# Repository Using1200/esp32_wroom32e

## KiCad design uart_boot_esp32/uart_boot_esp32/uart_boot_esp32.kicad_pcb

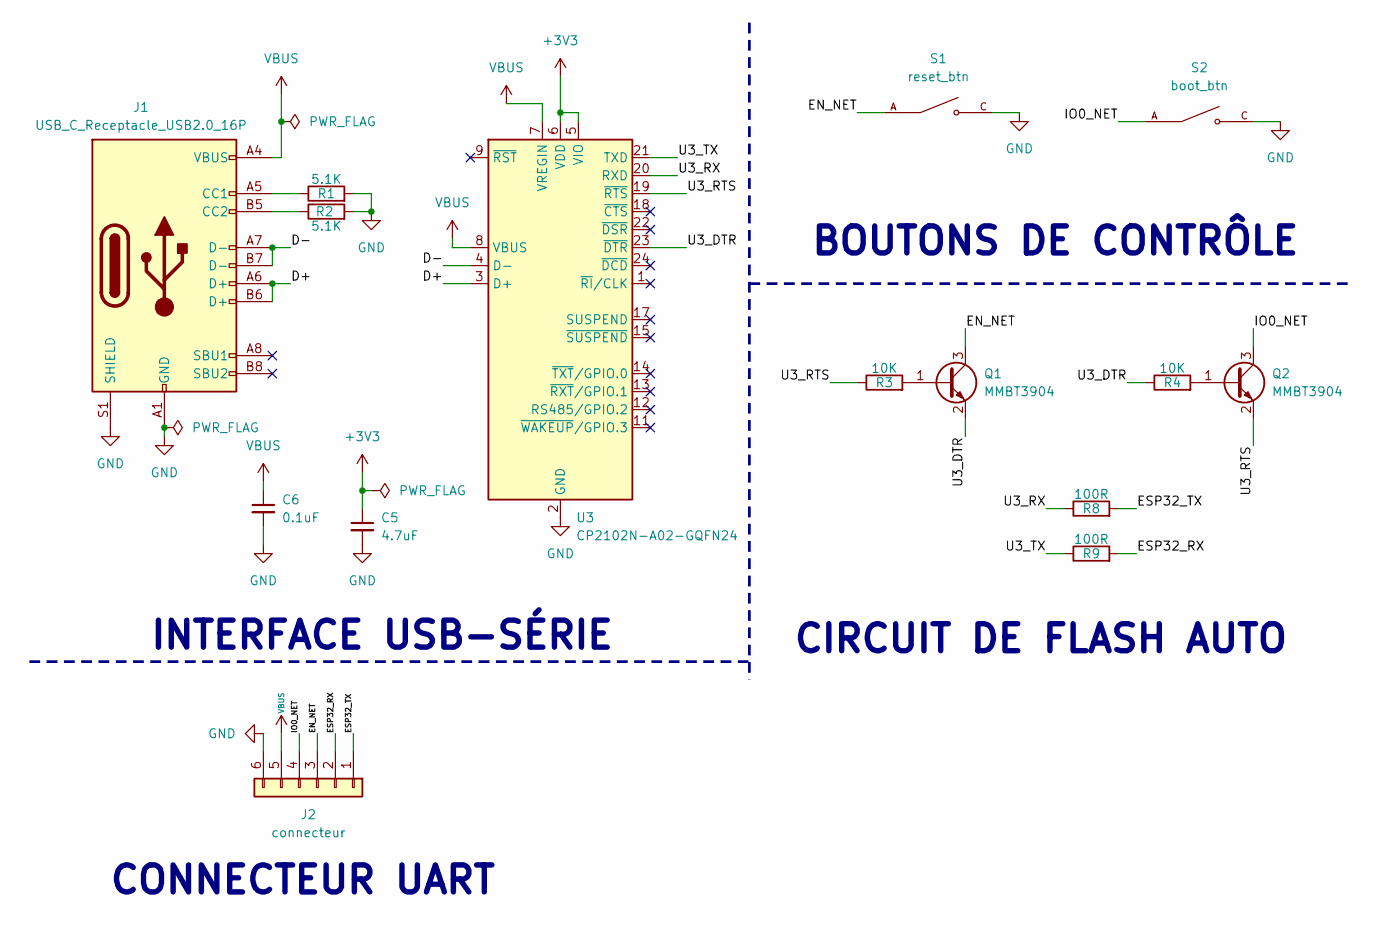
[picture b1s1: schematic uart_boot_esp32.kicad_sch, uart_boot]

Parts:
C5: 4.7uF; C_0603_1608Metric; LCSC C8032
C6: 0.1uF; C_0603_1608Metric; LCSC C14663
J1: USB_C_Receptacle_USB2.0_16P; USB_C_Receptacle_GCT_USB4105-xx-A_16P_TopMnt_Horizontal; LCSC C393939
J2: connecteur; Hirose_FH12-6S-0.5SH_1x06-1MP_P0.50mm_Horizontal
Q1, Q2: MMBT3904; SOT-23; LCSC C20526
R1, R2: 5.1K; R_0603_1608Metric; LCSC C23186
R3, R4: 10K; R_0603_1608Metric; LCSC C25804
R8, R9: 100R; R_0603_1608Metric; LCSC C22775
S1: reset_btn; SW_TS-1187A-B-A-B; PARTREV A0; LCSC C318884
S2: boot_btn; SW_TS-1187A-B-A-B; PARTREV A0; LCSC C318884
U3: CP2102N-A02-GQFN24; QFN-24-1EP_4x4mm_P0.5mm_EP2.6x2.6mm; LCSC C969151

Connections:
+3V3: C5.1, U3.5 (VIO), U3.6 (VDD)
/D+: J1.A6 (D+), J1.B6 (D+), U3.3 (D+)
/D-: J1.A7 (D-), J1.B7 (D-), U3.4 (D-)
/EN_NET: J2.3, Q1.3 (C), S1.A, S1.B
/ESP32_RX: J2.2, R9.2
/ESP32_TX: J2.1, R8.2
/IO0_NET: J2.4, Q2.3 (C), S2.A, S2.B
/U3_DTR: Q1.2 (E), R4.1, U3.23 (~DTR)
/U3_RTS: Q2.2 (E), R3.1, U3.19 (~RTS)
/U3_RX: R8.1, U3.20 (RXD)
/U3_TX: R9.1, U3.21 (TXD)
GND: C5.2, C6.2, J1.A1 (GND), J1.A12 (GND), J1.B1 (GND), J1.B12 (GND), J1.S1 (SHIELD), J2.6, R1.2, R2.2, S1.C, S1.D, S2.C, S2.D, U3.2 (GND), U3.25 (GND)
unnamed: J1.A5 (CC1), R1.1
unnamed: J1.B5 (CC2), R2.1
unnamed: Q1.1 (B), R3.2
unnamed: Q2.1 (B), R4.2
VBUS: C6.1, J1.A4 (VBUS), J1.A9 (VBUS), J1.B4 (VBUS), J1.B9 (VBUS), J2.5, U3.7 (VREGIN), U3.8 (VBUS)

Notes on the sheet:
CONNECTEUR UART
BOUTONS DE CONTRÔLE
CIRCUIT DE FLASH AUTO
INTERFACE USB-SÉRIE

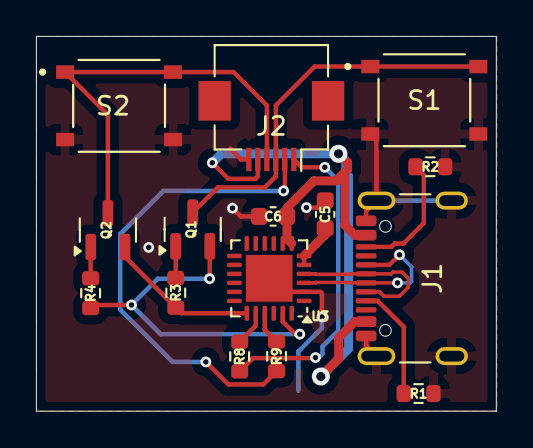
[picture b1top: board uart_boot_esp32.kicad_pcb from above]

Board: 2 copper layers, 25.6 x 20.8 mm, 15 parts (0 on the bottom side), 17 nets.

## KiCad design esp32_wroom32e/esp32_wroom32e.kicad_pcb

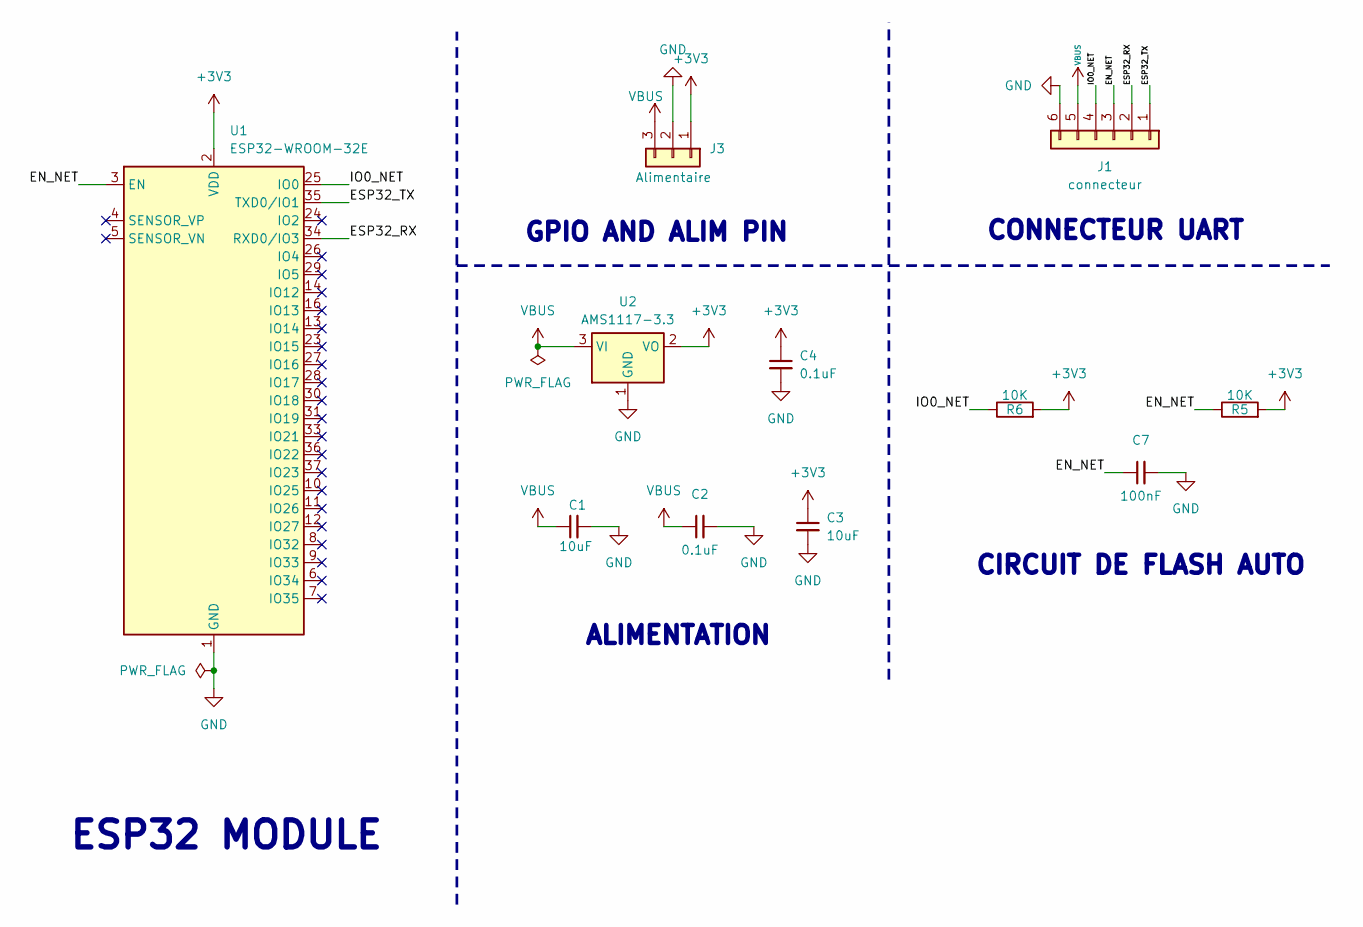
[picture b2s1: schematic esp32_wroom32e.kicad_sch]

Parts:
C1, C3: 10uF; C_0603_1608Metric; LCSC C19702
C2, C4: 0.1uF; C_0603_1608Metric; LCSC C14663
C7: 100nF; C_0603_1608Metric; LCSC C14663
J1: connecteur; Hirose_FH12-6S-0.5SH_1x06-1MP_P0.50mm_Horizontal
J3: Alimentaire; PinSocket_1x03_P2.54mm_Vertical
R5, R6: 10K; R_0603_1608Metric; LCSC C25804
U1: ESP32-WROOM-32E; LCSC C701341
U2: AMS1117-3.3; SOT-223-3_TabPin2; LCSC C6186

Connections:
+3V3: C3.1, C4.1, J3.1, R5.2, R6.2, U1.2 (VDD), U2.2 (VO)
/EN_NET: C7.1, J1.3, R5.1, U1.3 (EN)
/ESP32_RX: J1.2, U1.34 (RXD0/IO3)
/ESP32_TX: J1.1, U1.35 (TXD0/IO1)
/IO0_NET: J1.4, R6.1, U1.25 (IO0)
GND: C1.2, C2.2, C3.2, C4.2, C7.2, J1.6, J3.2, U1.1 (GND), U1.15 (GND), U1.38 (GND), U1.39 (GND), U2.1 (GND)
VBUS: C1.1, C2.1, J1.5, J3.3, U2.3 (VI)

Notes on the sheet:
GPIO AND ALIM PIN
ESP32 MODULE
CIRCUIT DE FLASH AUTO
ALIMENTATION
CONNECTEUR UART

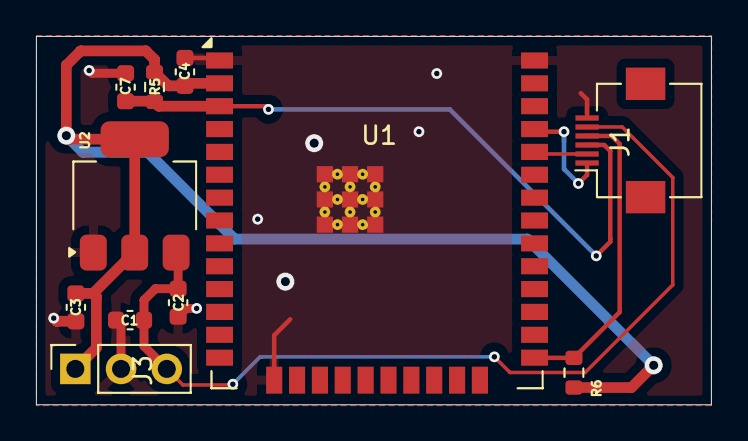
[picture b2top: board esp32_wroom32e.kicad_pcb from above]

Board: 2 copper layers, 37.5 x 20.5 mm, 11 parts (0 on the bottom side), 7 nets.
